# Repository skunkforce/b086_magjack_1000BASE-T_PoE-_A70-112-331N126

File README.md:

# edgy_board number b086
This design is part of the [edgy board project](https://github.com/skunkforce/edgy_boards).

# getting started
This repository uses submodules. After cloning use the command 

```$ git submodule update --init --recursive```

to pull the submodules before opening the project with kicad. 

# Tests
Tests can be found in [TESTS.md](TESTS.md)

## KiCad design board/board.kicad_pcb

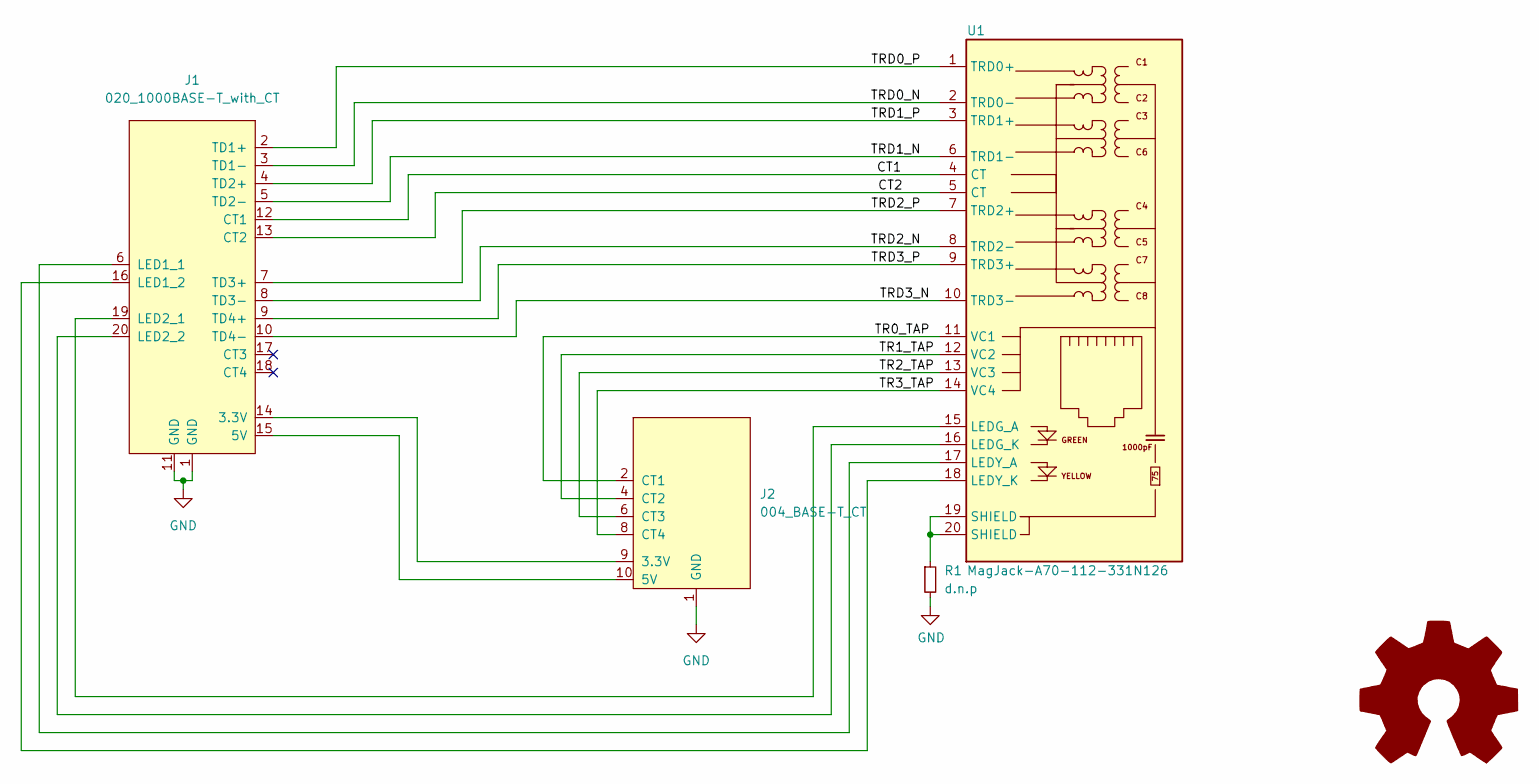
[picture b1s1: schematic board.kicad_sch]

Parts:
J1: 020_1000BASE-T_with_CT; on_edge_2x10_device
J2: 004_BASE-T_CT; on_edge_2x05_host
R1: d.n.p; R_1206_3216Metric
U1: MagJack-A70-112-331N126; TRJG0926HENL; Part Description Gigabit Ethernet Magjack
l1: Logo_Open_Hardware_Larg; OSHW-Logo2_7.3x6mm_SilkScreen

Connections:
/CT1: J1.12 (CT1), U1.4 (CT)
/CT2: J1.13 (CT2), U1.5 (CT)
/TR0_TAP: J2.2 (CT1), U1.11 (VC1)
/TR1_TAP: J2.4 (CT2), U1.12 (VC2)
/TR2_TAP: J2.6 (CT3), U1.13 (VC3)
/TR3_TAP: J2.8 (CT4), U1.14 (VC4)
/TRD0_N: J1.3 (TD1-), U1.2 (TRD0-)
/TRD0_P: J1.2 (TD1+), U1.1 (TRD0+)
/TRD1_N: J1.5 (TD2-), U1.6 (TRD1-)
/TRD1_P: J1.4 (TD2+), U1.3 (TRD1+)
/TRD2_N: J1.8 (TD3-), U1.8 (TRD2-)
/TRD2_P: J1.7 (TD3+), U1.7 (TRD2+)
/TRD3_N: J1.10 (TD4-), U1.10 (TRD3-)
/TRD3_P: J1.9 (TD4+), U1.9 (TRD3+)
GND: J1.1 (GND), J1.11 (GND), J2.1 (GND), R1.2
unnamed: J1.14 (3.3V), J2.9 (3.3V)
unnamed: J1.15 (5V), J2.10 (5V)
unnamed: R1.1, U1.19 (SHIELD), U1.20 (SHIELD)
unnamed: J1.19 (LED2_1), U1.15 (LEDG_A)
unnamed: J1.20 (LED2_2), U1.16 (LEDG_K)
unnamed: J1.6 (LED1_1), U1.17 (LEDY_A)
unnamed: J1.16 (LED1_2), U1.18 (LEDY_K)

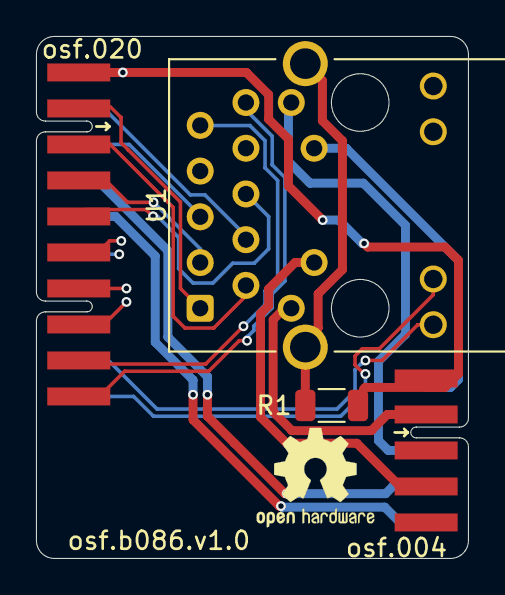
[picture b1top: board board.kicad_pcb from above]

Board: 4 copper layers, 24.0 x 29.0 mm, 5 parts (0 on the bottom side), 22 nets.

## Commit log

2023-03-04 initial
2023-03-08 led lines were backwards, fixed
